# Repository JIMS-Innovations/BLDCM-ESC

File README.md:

This repository contains the firmware, design files and documents for a Sensorless Electronic Speed Controller (for brushless DC motors) developed by Jesutofunmi Kupoluyi.

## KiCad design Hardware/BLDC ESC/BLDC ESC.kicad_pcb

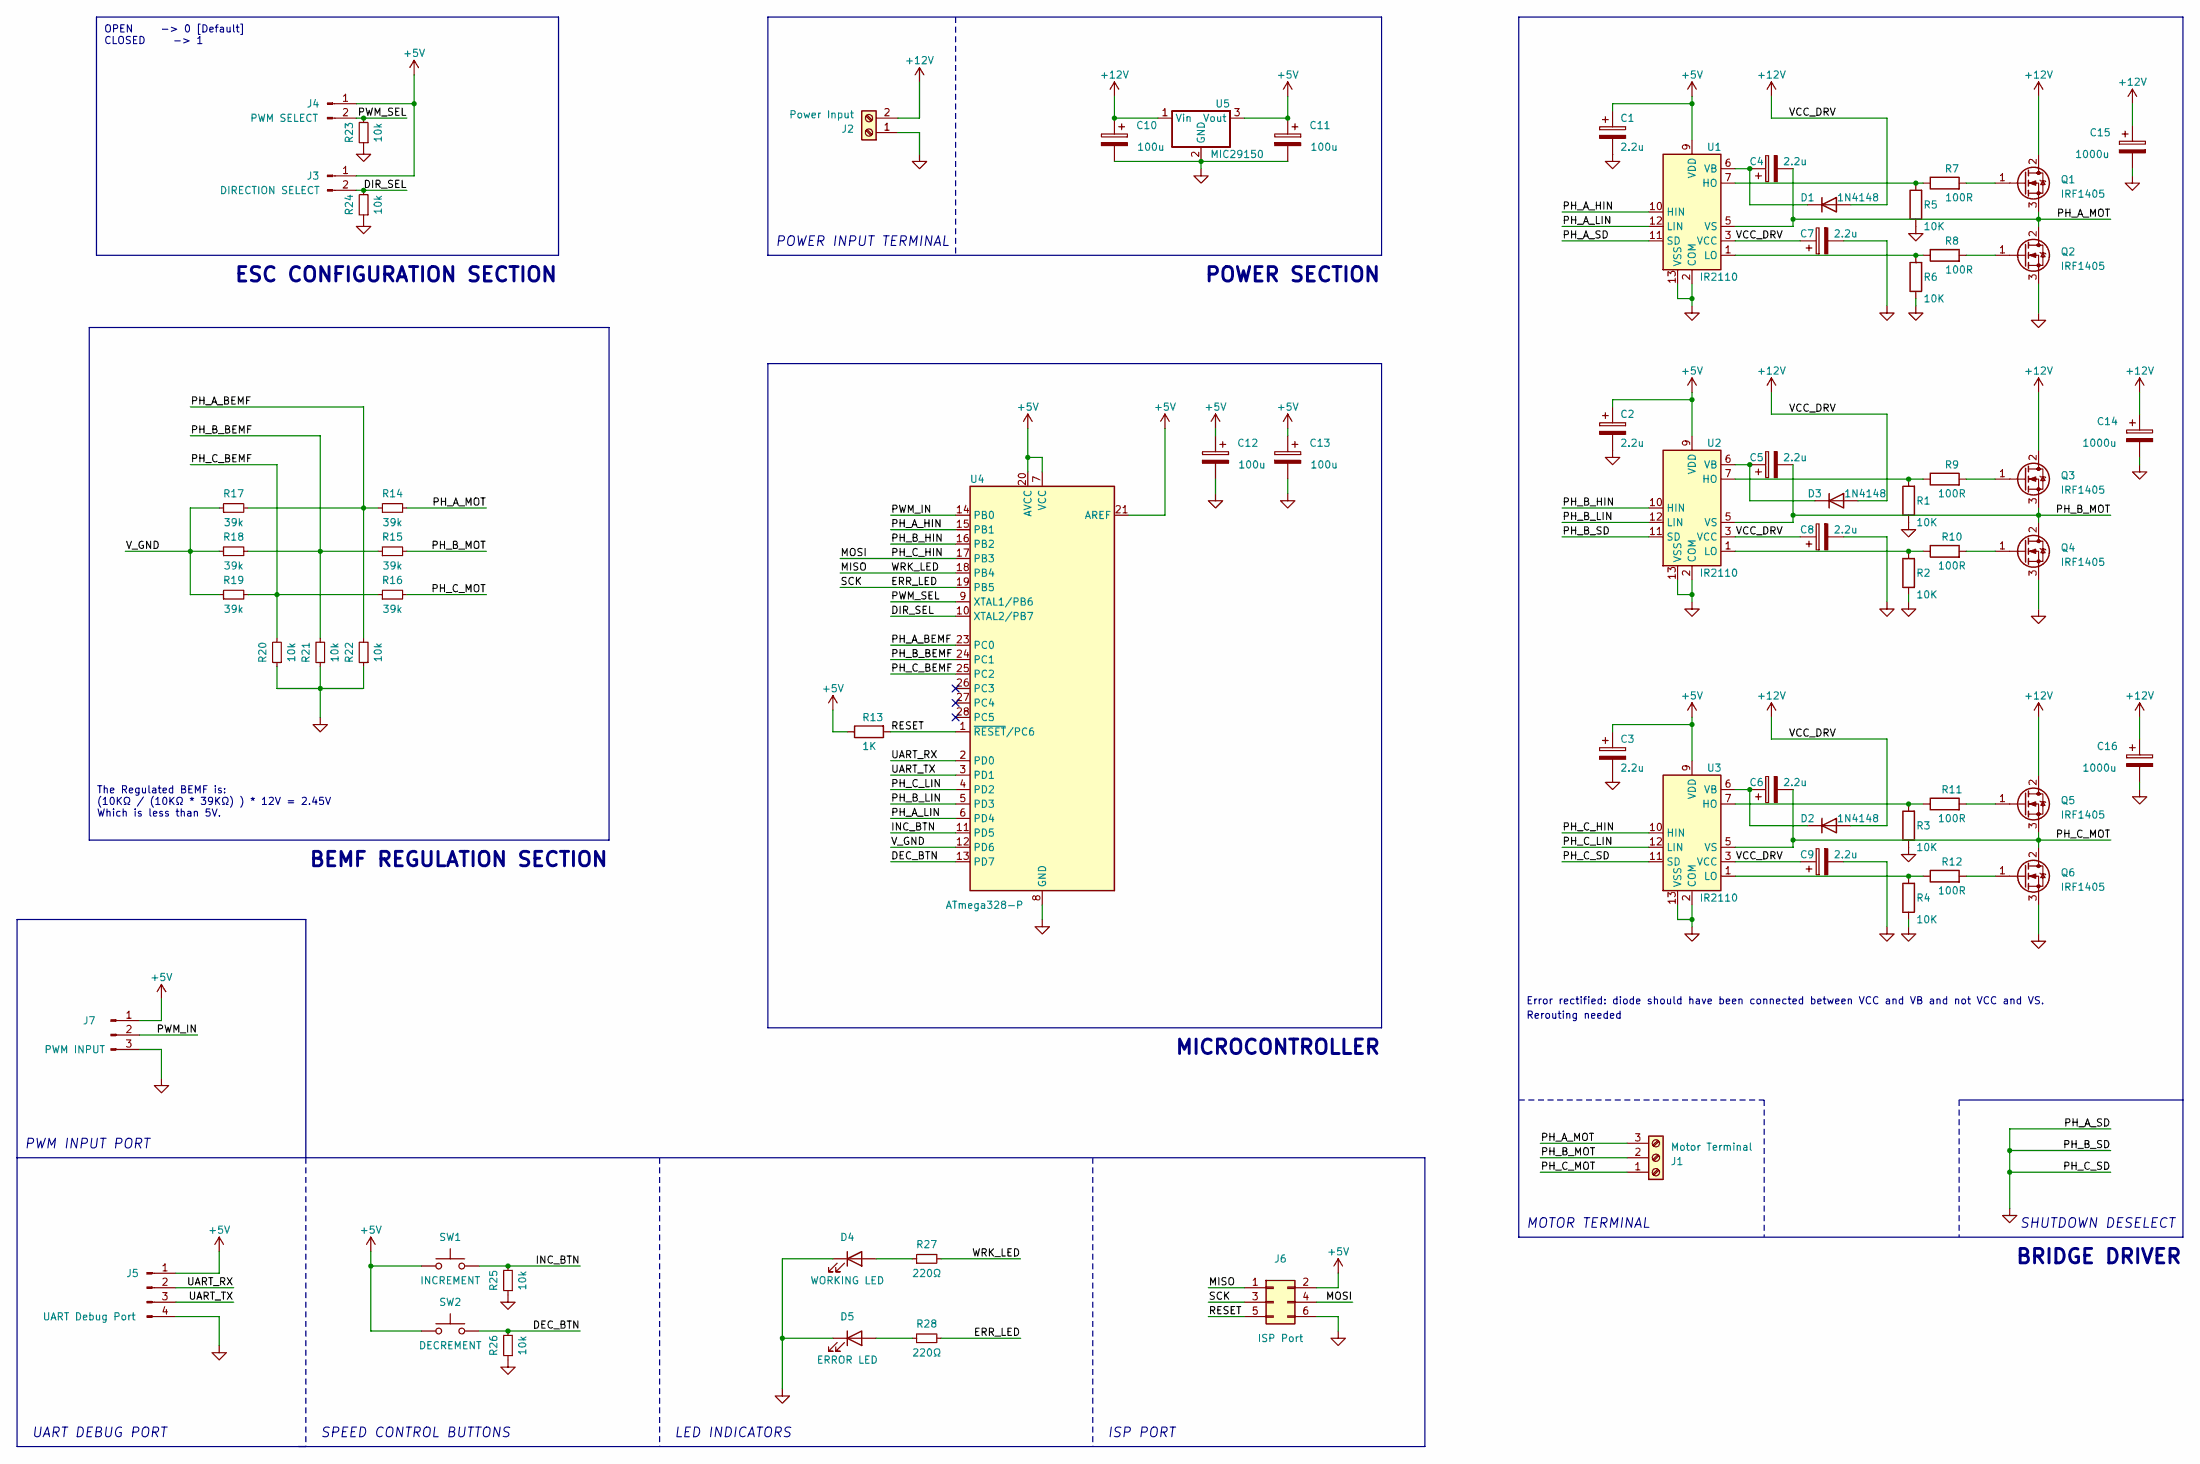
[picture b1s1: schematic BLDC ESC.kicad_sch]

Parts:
C1, C2, C3, C4, C5, C6, C7, C8, C9: 2.2u; CP_Radial_D5.0mm_P2.00mm
C10, C11, C12, C13: 100u; CP_Radial_D5.0mm_P2.50mm
C14, C15, C16: 1000u; CP_Radial_D14.0mm_P7.50mm
D1, D2, D3: 1N4148; D_A-405_P10.16mm_Horizontal
D4: WORKING LED; LED_D5.0mm
D5: ERROR LED; LED_D5.0mm
J1: Motor Terminal; TerminalBlock_bornier-3_P5.08mm
J2: Power Input; TerminalBlock_bornier-2_P5.08mm
J3: DIRECTION SELECT; PinHeader_1x02_P2.54mm_Vertical
J4: PWM SELECT; PinHeader_1x02_P2.54mm_Vertical
J5: UART Debug Port; PinHeader_1x04_P2.54mm_Vertical
J6: ISP Port; PinHeader_2x03_P2.54mm_Vertical
J7: PWM INPUT; PinHeader_1x03_P2.54mm_Vertical
Q1, Q2, Q3, Q4, Q5, Q6: IRF1405; TO-220-3_Vertical
R1, R2, R3, R4, R5, R6: 10K; R_Axial_DIN0207_L6.3mm_D2.5mm_P10.16mm_Horizontal
R7, R8, R9, R10, R11, R12: 100R; R_Axial_DIN0207_L6.3mm_D2.5mm_P10.16mm_Horizontal
R13: 1K; R_Axial_DIN0207_L6.3mm_D2.5mm_P10.16mm_Horizontal
R14, R15, R16, R17, R18, R19: 39k; R_Axial_DIN0207_L6.3mm_D2.5mm_P10.16mm_Horizontal
R20, R21, R22, R23, R24, R25, R26: 10k; R_Axial_DIN0207_L6.3mm_D2.5mm_P10.16mm_Horizontal
R27, R28: 220Ω; R_Axial_DIN0207_L6.3mm_D2.5mm_P10.16mm_Horizontal
SW1: INCREMENT; SW_PUSH_6mm
SW2: DECREMENT; SW_PUSH_6mm
U1, U2, U3: IR2110; DIP-14_W7.62mm
U4: ATmega328-P; DIP-28_W7.62mm
U5: MIC29150; TO-220-3_Vertical

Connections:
+5V: C1.1, C2.1, C3.1, C11.1, C12.1, C13.1, J3.1, J4.1, J5.1, J6.2, J7.1, R13.1, SW1.1, SW2.1, U1.9 (VDD), U2.9 (VDD), U3.9 (VDD), U4.7 (VCC), U4.20 (AVCC), U4.21 (AREF), U5.3 (Vout)
+12V: C7.1, C8.1, C9.1, C10.1, C14.1, C15.1, C16.1, D1.2 (A), D2.2 (A), D3.2 (A), J2.2, Q1.2 (D), Q3.2 (D), Q5.2 (D), U1.3 (VCC), U2.3 (VCC), U3.3 (VCC), U5.1 (Vin)
/DEC_BTN: R26.2, SW2.2, U4.13 (PD7)
/DIR_SEL: J3.2, R24.2, U4.10 (XTAL2/PB7)
/ERR_LED: J6.3, R28.2, U4.19 (PB5)
/INC_BTN: R25.2, SW1.2, U4.11 (PD5)
/MISO: J6.1, R27.2, U4.18 (PB4)
/MOSI: J6.4, U3.10 (HIN), U4.17 (PB3)
/PH_A_BEMF: R14.1, R17.2, R22.2, U4.23 (PC0)
/PH_A_HIN: U1.10 (HIN), U4.15 (PB1)
/PH_A_LIN: U1.12 (LIN), U4.6 (PD4)
/PH_A_MOT: C4.2, J1.3, Q1.3 (S), Q2.2 (D), R14.2, U1.5 (VS)
/PH_B_BEMF: R15.1, R18.2, R21.2, U4.24 (PC1)
/PH_B_HIN: U2.10 (HIN), U4.16 (PB2)
/PH_B_LIN: U2.12 (LIN), U4.5 (PD3)
/PH_B_MOT: C5.2, J1.2, Q3.3 (S), Q4.2 (D), R15.2, U2.5 (VS)
/PH_C_BEMF: R16.1, R19.2, R20.2, U4.25 (PC2)
/PH_C_LIN: U3.12 (LIN), U4.4 (PD2)
/PH_C_MOT: C6.2, J1.1, Q5.3 (S), Q6.2 (D), R16.2, U3.5 (VS)
/PWM_IN: J7.2, U4.14 (PB0)
/PWM_SEL: J4.2, R23.2, U4.9 (XTAL1/PB6)
/RESET: J6.5, R13.2, U4.1 (~RESET/PC6)
/UART_RX: J5.2, U4.2 (PD0)
/UART_TX: J5.3, U4.3 (PD1)
/V_GND: R17.1, R18.1, R19.1, U4.12 (PD6)
GND: C1.2, C2.2, C3.2, C7.2, C8.2, C9.2, C10.2, C11.2, C12.2, C13.2, C14.2, C15.2, C16.2, D4.1 (K), D5.1 (K), J2.1, J5.4, J6.6, J7.3, Q2.3 (S), Q4.3 (S), Q6.3 (S), R1.1, R2.1, R3.1, R4.1, R5.1, R6.1, R20.1, R21.1, R22.1, R23.1, R24.1, R25.1, R26.1, U1.2 (COM), U1.11 (SD), U1.13 (VSS), U2.2 (COM), U2.11 (SD), U2.13 (VSS), U3.2 (COM), U3.11 (SD), U3.13 (VSS), U4.8 (GND), U4.22 (GND), U5.2 (GND)
unnamed: C4.1, D1.1 (K), U1.6 (VB)
unnamed: C6.1, D2.1 (K), U3.6 (VB)
unnamed: C5.1, D3.1 (K), U2.6 (VB)
unnamed: D4.2 (A), R27.1
unnamed: D5.2 (A), R28.1
unnamed: Q1.1 (G), R7.2
unnamed: Q2.1 (G), R8.2
unnamed: Q3.1 (G), R9.2
unnamed: Q4.1 (G), R10.2
unnamed: Q5.1 (G), R11.2
unnamed: Q6.1 (G), R12.2
unnamed: R5.2, R7.1, U1.7 (HO)
unnamed: R6.2, R8.1, U1.1 (LO)
unnamed: R1.2, R9.1, U2.7 (HO)
unnamed: R2.2, R10.1, U2.1 (LO)
unnamed: R3.2, R11.1, U3.7 (HO)
unnamed: R4.2, R12.1, U3.1 (LO)

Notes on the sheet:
SHUTDOWN DESELECT
UART DEBUG PORT
PWM INPUT PORT
BEMF REGULATION SECTION
POWER SECTION
The Regulated BEMF is: (10KΩ / (10KΩ * 39KΩ) ) * 12V = 2.45V Which is less than 5V.
Error rectified: diode should have been connected between VCC and VB and not VCC and VS.
POWER INPUT TERMINAL
MICROCONTROLLER
ISP PORT
BRIDGE DRIVER
LED INDICATORS
ESC CONFIGURATION SECTION
Rerouting needed
SPEED CONTROL BUTTONS
MOTOR TERMINAL
OPEN -> 0 [Default] CLOSED -> 1

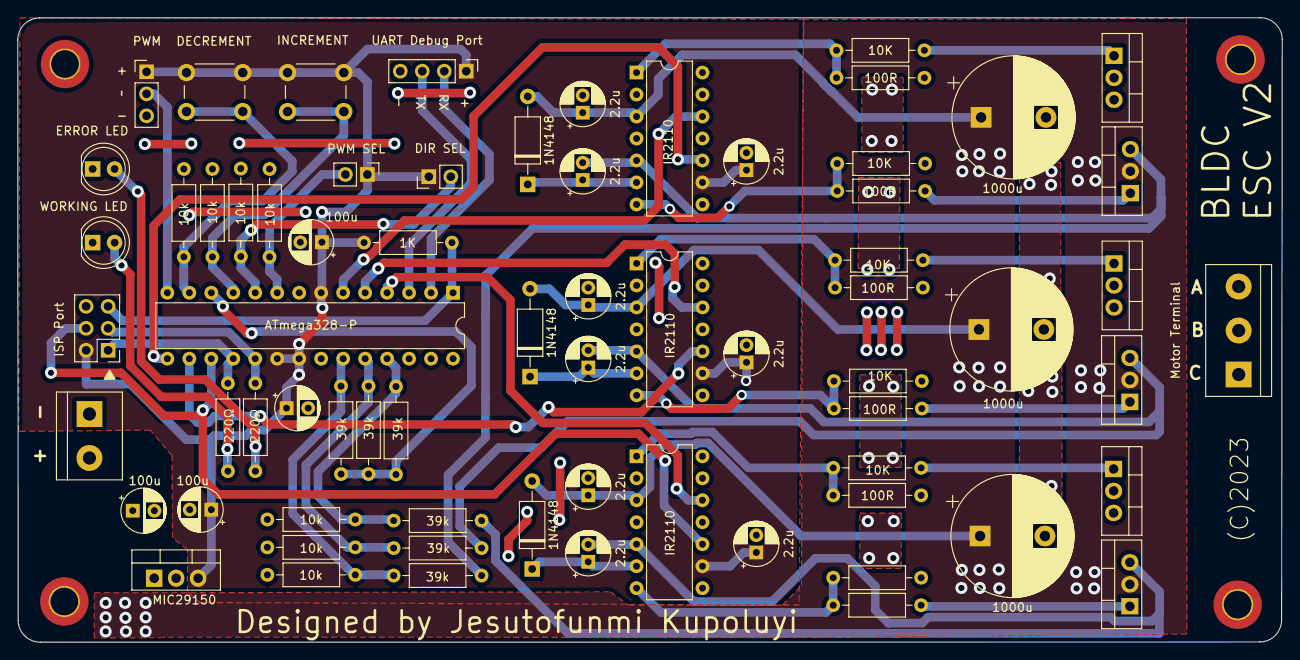
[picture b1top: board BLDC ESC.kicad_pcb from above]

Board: 2 copper layers, 146.2 x 72.2 mm, 69 parts (0 on the bottom side), 43 nets.

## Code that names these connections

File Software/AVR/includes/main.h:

/**
 * @file main.h
 * @author Jesutofunmi Kupoluyi (jimsufficiency@gmail.com)
 * @brief This is firmware header for my final year project - BLDC ESC
 * @version 0.1
 * @date 2023-10-17
 * 
 * @copyright Copyright (c) 2023
 * 
 */


#ifndef     __MAIN_H__
#define     __MAIN_H__

/* Definitions */
#define F_CPU 8000000UL /* CPU Clock frequency */
#define __AVR_ATmega328__
#define __DELAY_BACKWARD_COMPATIBLE__

/* Include required libraries */
#include <stdio.h>
#include <string.h>
#include <avr/io.h>
#include <avr/interrupt.h>
#include <util/delay.h>

/* Configuration definitions */
#define MAX_SPEED 255
#define MIN_SPEED 25 /* 35 */ 
#define START_SPEED 30 /* 75 */

/* Motor Phase Commutation sequence
    Step - 1 2 3 4 5 6
    High - A A B B C C 
    Low  - B C C A A B 
 */

/*** Bridge Pin definitions ***/
/* High Side */

#define A_H     PB1
#define B_H     PB2
#define C_H     PB3 /* * */
#define DRV_HS_DDR  DDRB
#define DRV_HS_PORT PORTB

/* Low Side */

#define A_L     PD4 /* * */
#define B_L     PD3
#define C_L     PD2 /* * */
#define DRV_LS_DDR  DDRD
#define DRV_LS_PORT PORTD

/***-----------------------***/

/* BEMF Sense Pins */
#define PH_A_BEMF   PC0
#define PH_B_BEMF   PC1
#define PH_C_BEMF   PC2
#define V_GND       PD6
#define BEMF_DDR    DDRC
#define BEMF_PORT   PORTC

/* PWM Input pin */
#define PWM_IN      PB0
#define PWN_DDR     DDRB
#define PWM_PORT    PORTB

/* LED Indicators */
#define WORKING_LED PB4
#define ERROR_LED   PB5
#define LED_DDR     DDRB
#define LED_PORT    PORTB

/* Mode Selection */
#define PWM_SEL     PB6
#define DIR_SEL     PB7
#define SEL_DDR     DDRB
#define SEL_PORT    PORTB

/* USART Port */
#define UART_RX     PD0
#define UART_TX     PD1

/* Speed Control Buttons */
#define INC_BTN     PD5
#define DEC_BTN     PD7
#define BTN_DDR     DDRD
#define BTN_PORT    PORTD
#define BTN_PIN     PIND

/* UART defines */
#define USART_BAUDRATE 9600 /* Set baud rate here */
#define BAUD_PRESCALE (((F_CPU / (USART_BAUDRATE * 16UL))) - 1)	


#endif    /*__MAIN_H__*/

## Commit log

2024-01-14 Basic features completed
2024-01-14 Basic feature completed
2024-01-14 Added README
2024-01-16 cleaned up code
2024-01-21 PCB errors corrected
2024-01-23 Update fabrication outputs
2024-02-15 Start up algorithm Update
